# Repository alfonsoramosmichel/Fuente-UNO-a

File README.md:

# Fuente-UNO-a
Fuente con salidas simétrica 12V; +5V y variable 4A.

Aún en desarrollo, no probada.

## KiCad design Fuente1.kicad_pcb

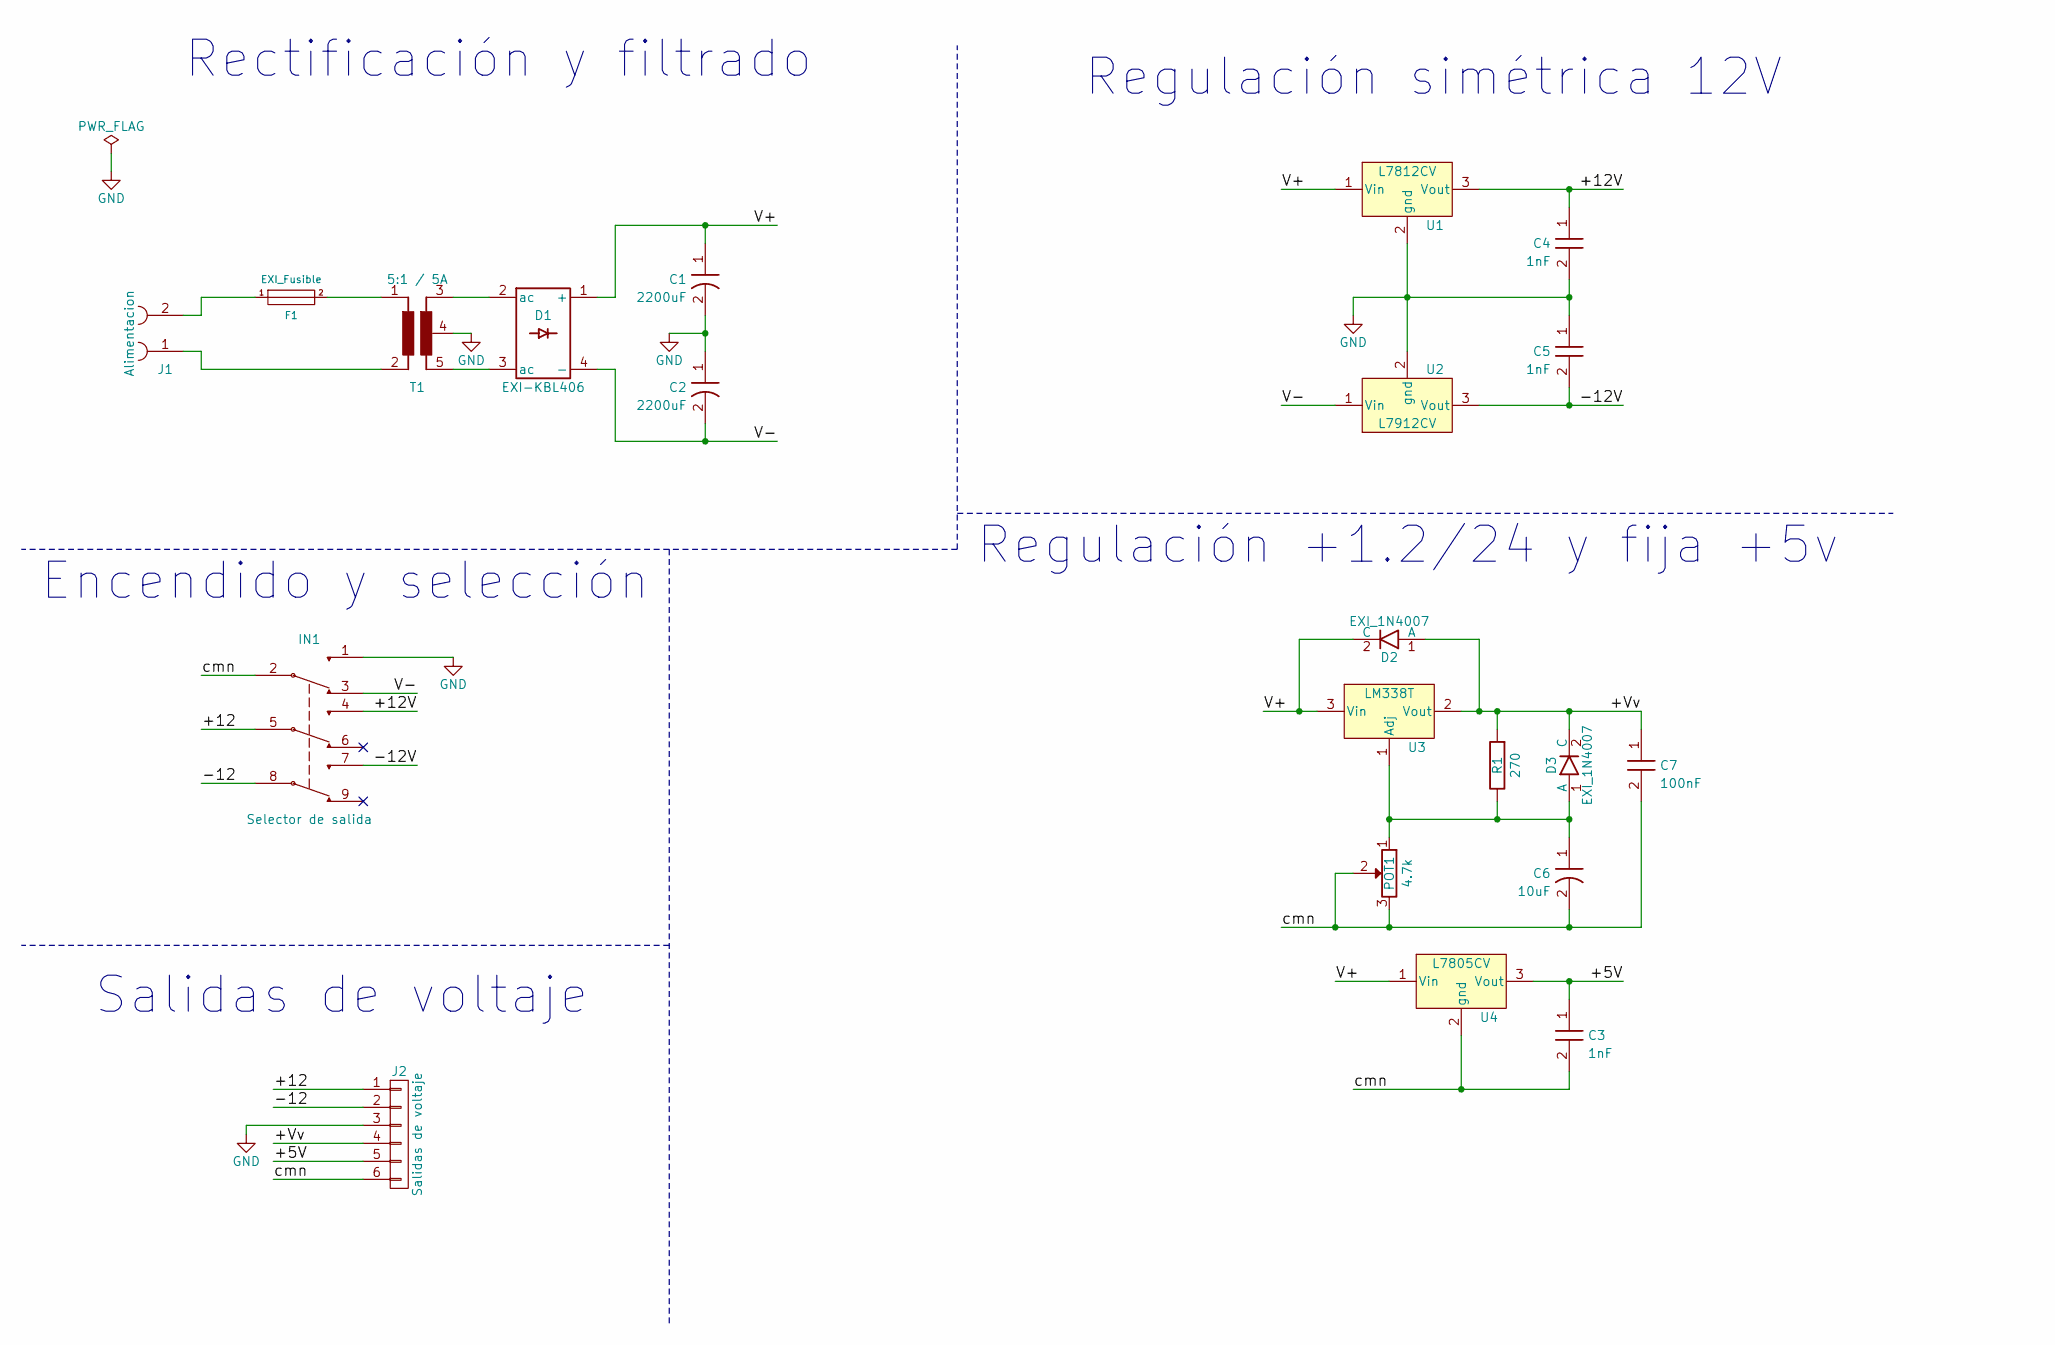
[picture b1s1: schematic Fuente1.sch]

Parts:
C1, C2: 2200uF; CP_Radial_D16.0mm_P7.50mm
C3, C4, C5: 1nF; C_Disc_D6.0mm_W2.5mm_P5.00mm
C6: 10uF; CP_Radial_D5.0mm_P2.50mm
C7: 100nF; C_Disc_D6.0mm_W2.5mm_P5.00mm
D1: EXI-KBL406; EXI_D3SB10
D2: EXI_1N4007; D_DO-41_SOD81_P7.62mm_Horizontal
D3: EXI_1N4007; D_DO-41_SOD81_P2.54mm_Vertical_AnodeUp
F1: EXI_Fusible; TerminalBlock_Pheonix_MPT-2.54mm_2pol
IN1: Selector de salida; Pin_Header_Straight_1x09_Pitch2.54mm
J1: Alimentacion; TerminalBlock_Pheonix_MPT-2.54mm_2pol
J2: Salidas de voltaje; EXI_Terminal_Hembra_1x06
POT1: 4.7k; EXI_Terminal_Hembra_1x03
R1: 270; R_Axial_DIN0309_L9.0mm_D3.2mm_P2.54mm_Vertical
T1: 5:1 / 5A; TerminalBlock_Pheonix_MPT-2.54mm_5pol
U1: L7812CV; TO-220-3_Horizontal_Heatsink_10x15x21mm
U2: L7912CV; TO-220-3_Horizontal_Heatsink_10x15x21mm
U3: LM338T; TO-220-3_Horizontal_Heatsink_10x15x21mm
U4: L7805CV; TO-220-3_Horizontal_Heatsink_10x15x21mm

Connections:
/+5V: C3.1, J2.5, U4.3 (Vout)
/+12: IN1.5, J2.1
/+12V: C4.1, IN1.4, U1.3 (Vout)
/+Vv: C7.1, D2.1 (A), D3.2 (C), J2.4, R1.1, U3.2 (Vout)
/-12: IN1.8, J2.2
/-12V: C5.2, IN1.7, U2.3 (Vout)
/V+: C1.1, D1.1 (+), D2.2 (C), U1.1 (Vin), U3.3 (Vin), U4.1 (Vin)
/V-: C2.2, D1.4 (-), IN1.3, U2.1 (Vin)
/cmn: C3.2, C6.2, C7.2, IN1.2, J2.6, POT1.2, POT1.3, U4.2 (gnd)
GND: C1.2, C2.1, C4.2, C5.1, IN1.1, J2.3, T1.4, U1.2 (gnd), U2.2 (gnd)
unnamed: C6.1, D3.1 (A), POT1.1, R1.2, U3.1 (Adj)
unnamed: D1.2 (ac), T1.3
unnamed: D1.3 (ac), T1.5
unnamed: F1.1, J1.2
unnamed: F1.2, T1.1
unnamed: J1.1, T1.2

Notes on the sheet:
Rectificación y filtrado
Encendido y selección
Salidas de voltaje
Regulación simétrica 12V
Regulación +1.2/24 y fija +5v

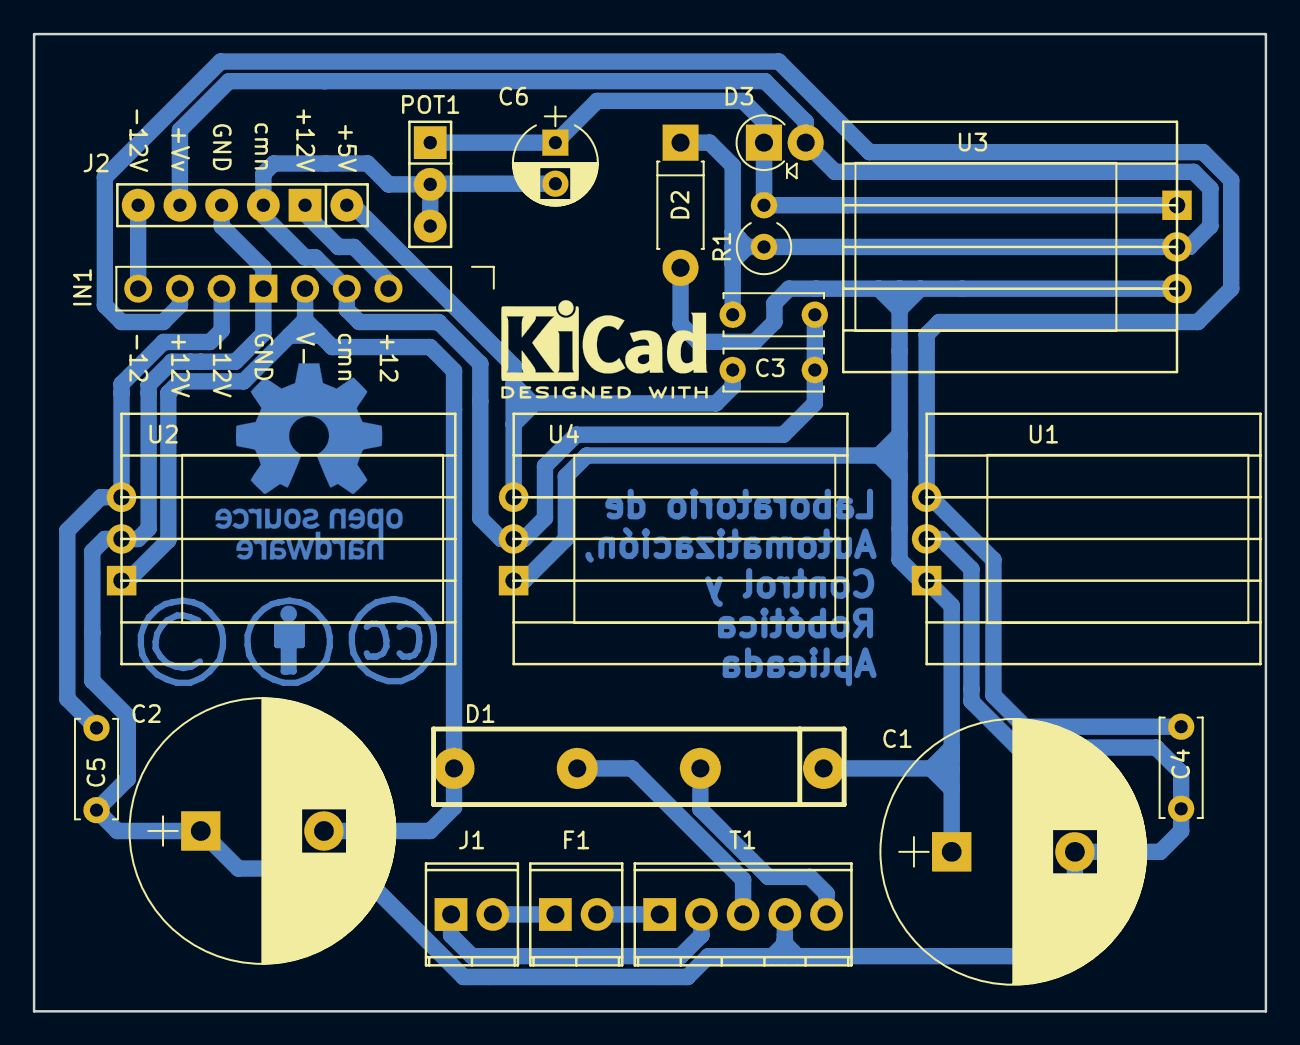
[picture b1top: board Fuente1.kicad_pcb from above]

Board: 2 copper layers, 75.0 x 59.5 mm, 21 parts (0 on the bottom side), 16 nets.

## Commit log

2017-12-02 Commit inicial
    Cambios para hacer commit:
    nuevo archivo: Fuente1-cache.lib
    nuevo archivo: Fuente1.bak
    nuevo archivo: Fuente1.cmp
    nuevo archivo: Fuente1.kicad_pcb
    nuevo archivo: Fuente1.kicad_pcb-bak
2017-12-08 *** Corrección de reguladores ***
    Cambios para hacer commit:
    modificado: Fuente1.bak
    modificado: Fuente1.kicad_pcb
    modificado: Fuente1.kicad_pcb-bak
    modificado: Fuente1.net
    renombrado: _saved_Fuente1.sch -> Fuente1.sch
2018-02-21 Seccionado
    Anotaciones de secciones en el esquemático
    Cambios para hacer commit:
    modificado: Fuente1.bak
    modificado: Fuente1.sch
